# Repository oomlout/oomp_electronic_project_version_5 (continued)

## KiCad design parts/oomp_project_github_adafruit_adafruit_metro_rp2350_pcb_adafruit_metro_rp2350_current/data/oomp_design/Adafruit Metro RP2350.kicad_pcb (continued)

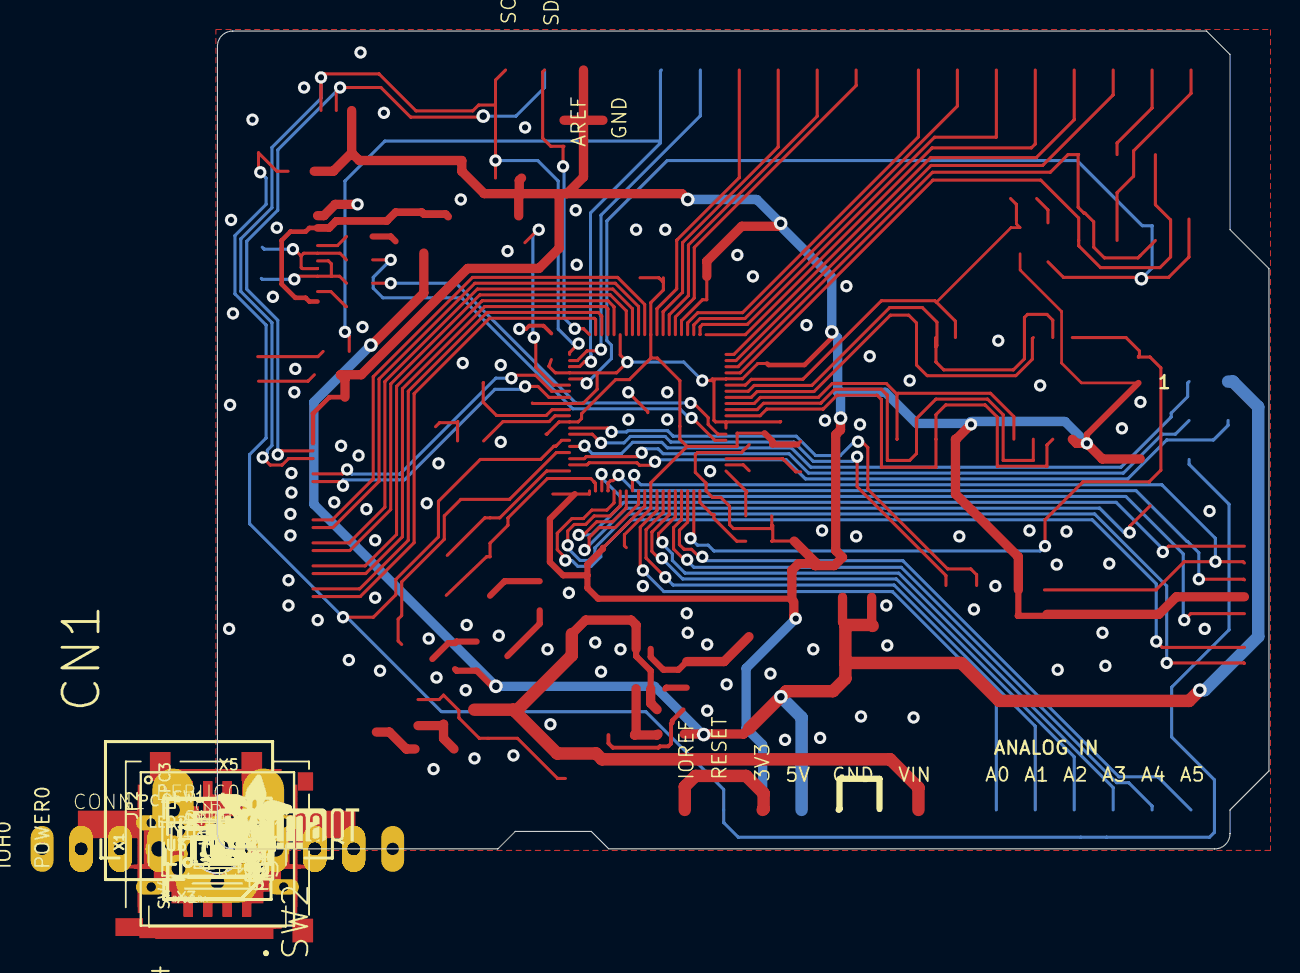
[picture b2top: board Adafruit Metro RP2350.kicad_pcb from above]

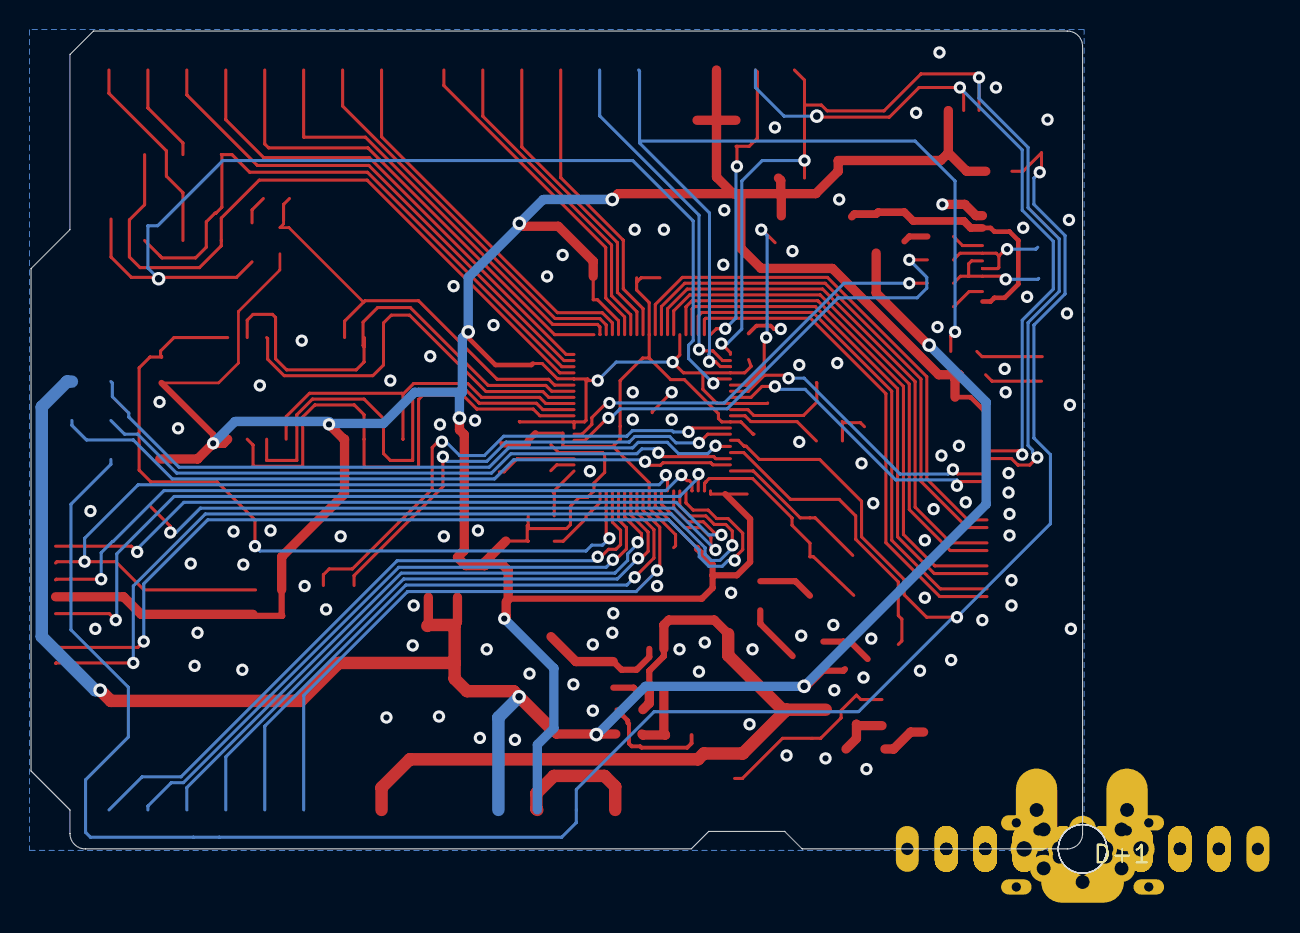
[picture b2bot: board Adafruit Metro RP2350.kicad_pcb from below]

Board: 2 copper layers, 68.6 x 53.3 mm, 174 parts (5 on the bottom side), 89 nets.

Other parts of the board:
PLABEL0: PLABEL0
PLABEL1: PLABEL1
PLABEL2: PLABEL2
PLABEL3: PLABEL3
PLABEL4: PLABEL4
PLABEL5: PLABEL5
PLABEL6: PLABEL6
PLABEL7: PLABEL7
PLABEL8: PLABEL8
PLABEL10: PLABEL10
PLABEL11: PLABEL11
PLABEL12: PLABEL12
PLABEL13: PLABEL13
PLABEL14: PLABEL14
PLABEL15: PLABEL15
PLABEL16: PLABEL16
PLABEL17: PLABEL17
PLABEL18: PLABEL18
PLABEL19: PLABEL19
PLABEL20: PLABEL20
PLABEL21: PLABEL21
PLABEL22: PLABEL22
PLABEL23: PLABEL23
PLABEL24: PLABEL24
PLABEL25: PLABEL25
PLABEL26: PLABEL26
PLABEL27: PLABEL27
PLABEL28: PLABEL28
PLABEL29: PLABEL29
PLABEL30: PLABEL30
PLABEL31: PLABEL31
PLABEL32: PLABEL32
PLABEL33: PLABEL33
PLABEL34: PLABEL34
PLABEL35: PLABEL35
PLABEL36: PLABEL36
PLABEL37: PLABEL37
PLABEL38: PLABEL38
PLABEL39: PLABEL39
PLABEL40: PLABEL40
PLABEL41: PLABEL41
PLABEL42: PLABEL42
PLABEL43: PLABEL43
PLABEL46: PLABEL46
PLABEL47: PLABEL47
PLABEL48: PLABEL48
PLABEL49: PLABEL49
PLABEL50: PLABEL50
PLABEL51: PLABEL51
PLABEL52: PLABEL52
PLABEL53: PLABEL53
PLABEL54: PLABEL54
PLABEL55: PLABEL55
PLABEL56: PLABEL56
PLABEL57: PLABEL57
PLABEL59: PLABEL59
PLABEL60: PLABEL60
PLABEL62: PLABEL62
PLABEL63: PLABEL63
PLABEL64: PLABEL64
PLABEL65: PLABEL65
PLABEL66: PLABEL66
PLABEL67: PLABEL67
PLABEL68: PLABEL68
PLABEL69: PLABEL69
PLABEL70: PLABEL70
U$3: STEMMAQT
U$11: PCBFEAT-REV-040
U$47: METRO_RP2350_TOP
U$50: ADAFRUIT_5MM
U$71: METRO_RP2350_BOT
UNK_HOLE_0: dummyfp0
UNK_HOLE_1: dummyfp1
UNK_HOLE_2: dummyfp2
UNK_HOLE_3: dummyfp3

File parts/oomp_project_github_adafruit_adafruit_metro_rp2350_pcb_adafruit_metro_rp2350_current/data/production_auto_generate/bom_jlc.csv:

Comment,Designator,Footprint,LCSC Part #
,JP1,Adafruit Metro RP2350-import-fps:1X01_ROUND,C7501259
,JP2,Adafruit Metro RP2350-import-fps:1X04_ROUND,C42431795
,U$50,Adafruit Metro RP2350-import-fps:ADAFRUIT_5MM,
,U$71,Adafruit Metro RP2350-import-fps:METRO_RP2350_BOT,
,U$47,Adafruit Metro RP2350-import-fps:METRO_RP2350_TOP,
,U$11,Adafruit Metro RP2350-import-fps:PCBFEAT-REV-040,
,PLABEL0,Adafruit Metro RP2350-import-fps:PLABEL0,
,PLABEL1,Adafruit Metro RP2350-import-fps:PLABEL1,
,PLABEL10,Adafruit Metro RP2350-import-fps:PLABEL10,
,PLABEL11,Adafruit Metro RP2350-import-fps:PLABEL11,
,PLABEL12,Adafruit Metro RP2350-import-fps:PLABEL12,
,PLABEL13,Adafruit Metro RP2350-import-fps:PLABEL13,
,PLABEL14,Adafruit Metro RP2350-import-fps:PLABEL14,
,PLABEL15,Adafruit Metro RP2350-import-fps:PLABEL15,
,PLABEL16,Adafruit Metro RP2350-import-fps:PLABEL16,
,PLABEL17,Adafruit Metro RP2350-import-fps:PLABEL17,
,PLABEL18,Adafruit Metro RP2350-import-fps:PLABEL18,
,PLABEL19,Adafruit Metro RP2350-import-fps:PLABEL19,
,PLABEL2,Adafruit Metro RP2350-import-fps:PLABEL2,
,PLABEL20,Adafruit Metro RP2350-import-fps:PLABEL20,
,PLABEL21,Adafruit Metro RP2350-import-fps:PLABEL21,
,PLABEL22,Adafruit Metro RP2350-import-fps:PLABEL22,
,PLABEL23,Adafruit Metro RP2350-import-fps:PLABEL23,
,PLABEL24,Adafruit Metro RP2350-import-fps:PLABEL24,
,PLABEL25,Adafruit Metro RP2350-import-fps:PLABEL25,
,PLABEL26,Adafruit Metro RP2350-import-fps:PLABEL26,
,PLABEL27,Adafruit Metro RP2350-import-fps:PLABEL27,
,PLABEL28,Adafruit Metro RP2350-import-fps:PLABEL28,
,PLABEL29,Adafruit Metro RP2350-import-fps:PLABEL29,
,PLABEL3,Adafruit Metro RP2350-import-fps:PLABEL3,
,PLABEL30,Adafruit Metro RP2350-import-fps:PLABEL30,
,PLABEL31,Adafruit Metro RP2350-import-fps:PLABEL31,
,PLABEL32,Adafruit Metro RP2350-import-fps:PLABEL32,
,PLABEL33,Adafruit Metro RP2350-import-fps:PLABEL33,
,PLABEL34,Adafruit Metro RP2350-import-fps:PLABEL34,
,PLABEL35,Adafruit Metro RP2350-import-fps:PLABEL35,
,PLABEL36,Adafruit Metro RP2350-import-fps:PLABEL36,
,PLABEL37,Adafruit Metro RP2350-import-fps:PLABEL37,
,PLABEL38,Adafruit Metro RP2350-import-fps:PLABEL38,
,PLABEL39,Adafruit Metro RP2350-import-fps:PLABEL39,
,PLABEL4,Adafruit Metro RP2350-import-fps:PLABEL4,
,PLABEL40,Adafruit Metro RP2350-import-fps:PLABEL40,
,PLABEL41,Adafruit Metro RP2350-import-fps:PLABEL41,
,PLABEL42,Adafruit Metro RP2350-import-fps:PLABEL42,
,PLABEL43,Adafruit Metro RP2350-import-fps:PLABEL43,
,PLABEL46,Adafruit Metro RP2350-import-fps:PLABEL46,
,PLABEL47,Adafruit Metro RP2350-import-fps:PLABEL47,
,PLABEL48,Adafruit Metro RP2350-import-fps:PLABEL48,
,PLABEL49,Adafruit Metro RP2350-import-fps:PLABEL49,
,PLABEL5,Adafruit Metro RP2350-import-fps:PLABEL5,
,PLABEL50,Adafruit Metro RP2350-import-fps:PLABEL50,
,PLABEL51,Adafruit Metro RP2350-import-fps:PLABEL51,
,PLABEL52,Adafruit Metro RP2350-import-fps:PLABEL52,
,PLABEL53,Adafruit Metro RP2350-import-fps:PLABEL53,
,PLABEL54,Adafruit Metro RP2350-import-fps:PLABEL54,
,PLABEL55,Adafruit Metro RP2350-import-fps:PLABEL55,
,PLABEL56,Adafruit Metro RP2350-import-fps:PLABEL56,
,PLABEL57,Adafruit Metro RP2350-import-fps:PLABEL57,
,PLABEL59,Adafruit Metro RP2350-import-fps:PLABEL59,
,PLABEL6,Adafruit Metro RP2350-import-fps:PLABEL6,
,PLABEL60,Adafruit Metro RP2350-import-fps:PLABEL60,
,PLABEL62,Adafruit Metro RP2350-import-fps:PLABEL62,
,PLABEL63,Adafruit Metro RP2350-import-fps:PLABEL63,
,PLABEL64,Adafruit Metro RP2350-import-fps:PLABEL64,
,PLABEL65,Adafruit Metro RP2350-import-fps:PLABEL65,
,PLABEL66,Adafruit Metro RP2350-import-fps:PLABEL66,
,PLABEL67,Adafruit Metro RP2350-import-fps:PLABEL67,
,PLABEL68,Adafruit Metro RP2350-import-fps:PLABEL68,
,PLABEL69,Adafruit Metro RP2350-import-fps:PLABEL69,
,PLABEL7,Adafruit Metro RP2350-import-fps:PLABEL7,
,PLABEL70,Adafruit Metro RP2350-import-fps:PLABEL70,
,PLABEL8,Adafruit Metro RP2350-import-fps:PLABEL8,
,U$3,Adafruit Metro RP2350-import-fps:STEMMAQT,
,TP1,Adafruit Metro RP2350-import-fps:TESTPOINT_ROUND_1.5MM_NO,
0.1uF,"C6,C7,C8,C13,C14,C17,C21,C22,C23,C24,C25,C29,C30,C33",Adafruit Metro RP2350-import-fps:0603-NO,C14663
10,R5,Adafruit Metro RP2350-import-fps:0603-NO,C22859
10K,"R1,R2,R3,R6,R7,R8,R10,R12,R13,R17,R21",Adafruit Metro RP2350-import-fps:0603-NO,C98220
10uF,"C3,C5,C9,C18,C19,C20,C31,C32",Adafruit Metro RP2350-import-fps:0805-NO,
10uF_0603,"C10,C15",Adafruit Metro RP2350-import-fps:0603-NO_WIDE,C19702
12MHz_10pF_50ohm,Y1,Adafruit Metro RP2350-import-fps:CRYSTAL_2.5X2,
15pF,"C26,C27",Adafruit Metro RP2350-import-fps:0603-NO,
1K,"R23,R26",Adafruit Metro RP2350-import-fps:0603-NO,C2907002
1N4148,D3,Adafruit Metro RP2350-import-fps:SOD-323,
1uF,"C2,C11,C12,C16,C28",Adafruit Metro RP2350-import-fps:0603-NO,C5673
2.1mm,X5,Adafruit Metro RP2350-import-fps:DCJACK_2MM_PTH,
2.2K,R11,Adafruit Metro RP2350-import-fps:0603-NO,C4190
2.2uF,"C1,C4",Adafruit Metro RP2350-import-fps:0603-NO,C23630
200,R4,Adafruit Metro RP2350-import-fps:0603-NO,C114664
20609,AD0,Adafruit Metro RP2350-import-fps:1X06_OVALWAVE,C37208
20610,"IOL0,POWER0",Adafruit Metro RP2350-import-fps:1X08_OVALWAVE,C492421
20611,IOH0,Adafruit Metro RP2350-import-fps:1X10_OVALWAVE,C57369
22 ohm,"R24,R25",Adafruit Metro RP2350-import-fps:0603-NO,C23345
220uF/6.3V,PC4,Adafruit Metro RP2350-import-fps:PANASONIC_D,
22p BOTTOM 0.5mm FPC,CN1,Adafruit Metro RP2350-import-fps:FPC_22PIN,
3.3uH 5A 20mOhm,L2,Adafruit Metro RP2350-import-fps:INDUCTOR_0603S,
3x2 M,ICSP0,Adafruit Metro RP2350-import-fps:2X03_ROUND_70MIL,
47uF/25V,PC3,Adafruit Metro RP2350-import-fps:PANASONIC_D,
5.1K,"R19,R20",Adafruit Metro RP2350-import-fps:0603-NO,C23186
56K,R9,Adafruit Metro RP2350-import-fps:0603-NO,C23206
5V/1A,PTC1,Adafruit Metro RP2350-import-fps:0805-NO,
AP2112K-3.3,U2,Adafruit Metro RP2350-import-fps:SOT23-DBV,
BSS138,Q1,Adafruit Metro RP2350-import-fps:SOT23-WIDE,C52895
DFE252012F-3R3M=P2,L1,Adafruit Metro RP2350-import-fps:INDUCTOR_1007,
DMP3098L,"T1,T2",Adafruit Metro RP2350-import-fps:SOT23-WIDE,
DNP,"R14,R15",Adafruit Metro RP2350-import-fps:0603-NO,
DNP,U3,Adafruit Metro RP2350-import-fps:SOIC8_208MIL,
DPDT,SW4,Adafruit Metro RP2350-import-fps:EG1390,
FIDUCIAL_1MM,"FD1,FD2,FD3",Adafruit Metro RP2350-import-fps:FIDUCIAL_1MM,
GREEN,ON0,Adafruit Metro RP2350-import-fps:CHIPLED_0603_NOOUTLINE,
JST_SH3,DEBUG0,Adafruit Metro RP2350-import-fps:JST_SH3_RA,
MICROSD,X1,Adafruit Metro RP2350-import-fps:MOLEX_104031-0811,
PMEG2020,"D1,D2",Adafruit Metro RP2350-import-fps:SOD-323,
RED,L0,Adafruit Metro RP2350-import-fps:CHIPLED_0603_NOOUTLINE,
RP2350B,X4,Adafruit Metro RP2350-import-fps:QFN80,
SPDT_RA,SW1,Adafruit Metro RP2350-import-fps:SPDT_SMT_SSSS811101,
STEMMA_I2C_QT,CONN1,Adafruit Metro RP2350-import-fps:JST_SH4,C160404
SW_RA,"SW2,SW3",Adafruit Metro RP2350-import-fps:SPST_TACTILE_RA,
"TPB1,27","D+1,D-1","Adafruit Metro RP2350-import-fps:B1,27",
TPS563201,IC1,Adafruit Metro RP2350-import-fps:SOT23-6,
USB Type C,X3,Adafruit Metro RP2350-import-fps:USB_C_CUSB31-CFM2AX-01-X,
W25Q128,U6,Adafruit Metro RP2350-import-fps:SOIC8_208MIL,
WS2812B_3535FULL,LED2,Adafruit Metro RP2350-import-fps:LED3535_FULLPADS,

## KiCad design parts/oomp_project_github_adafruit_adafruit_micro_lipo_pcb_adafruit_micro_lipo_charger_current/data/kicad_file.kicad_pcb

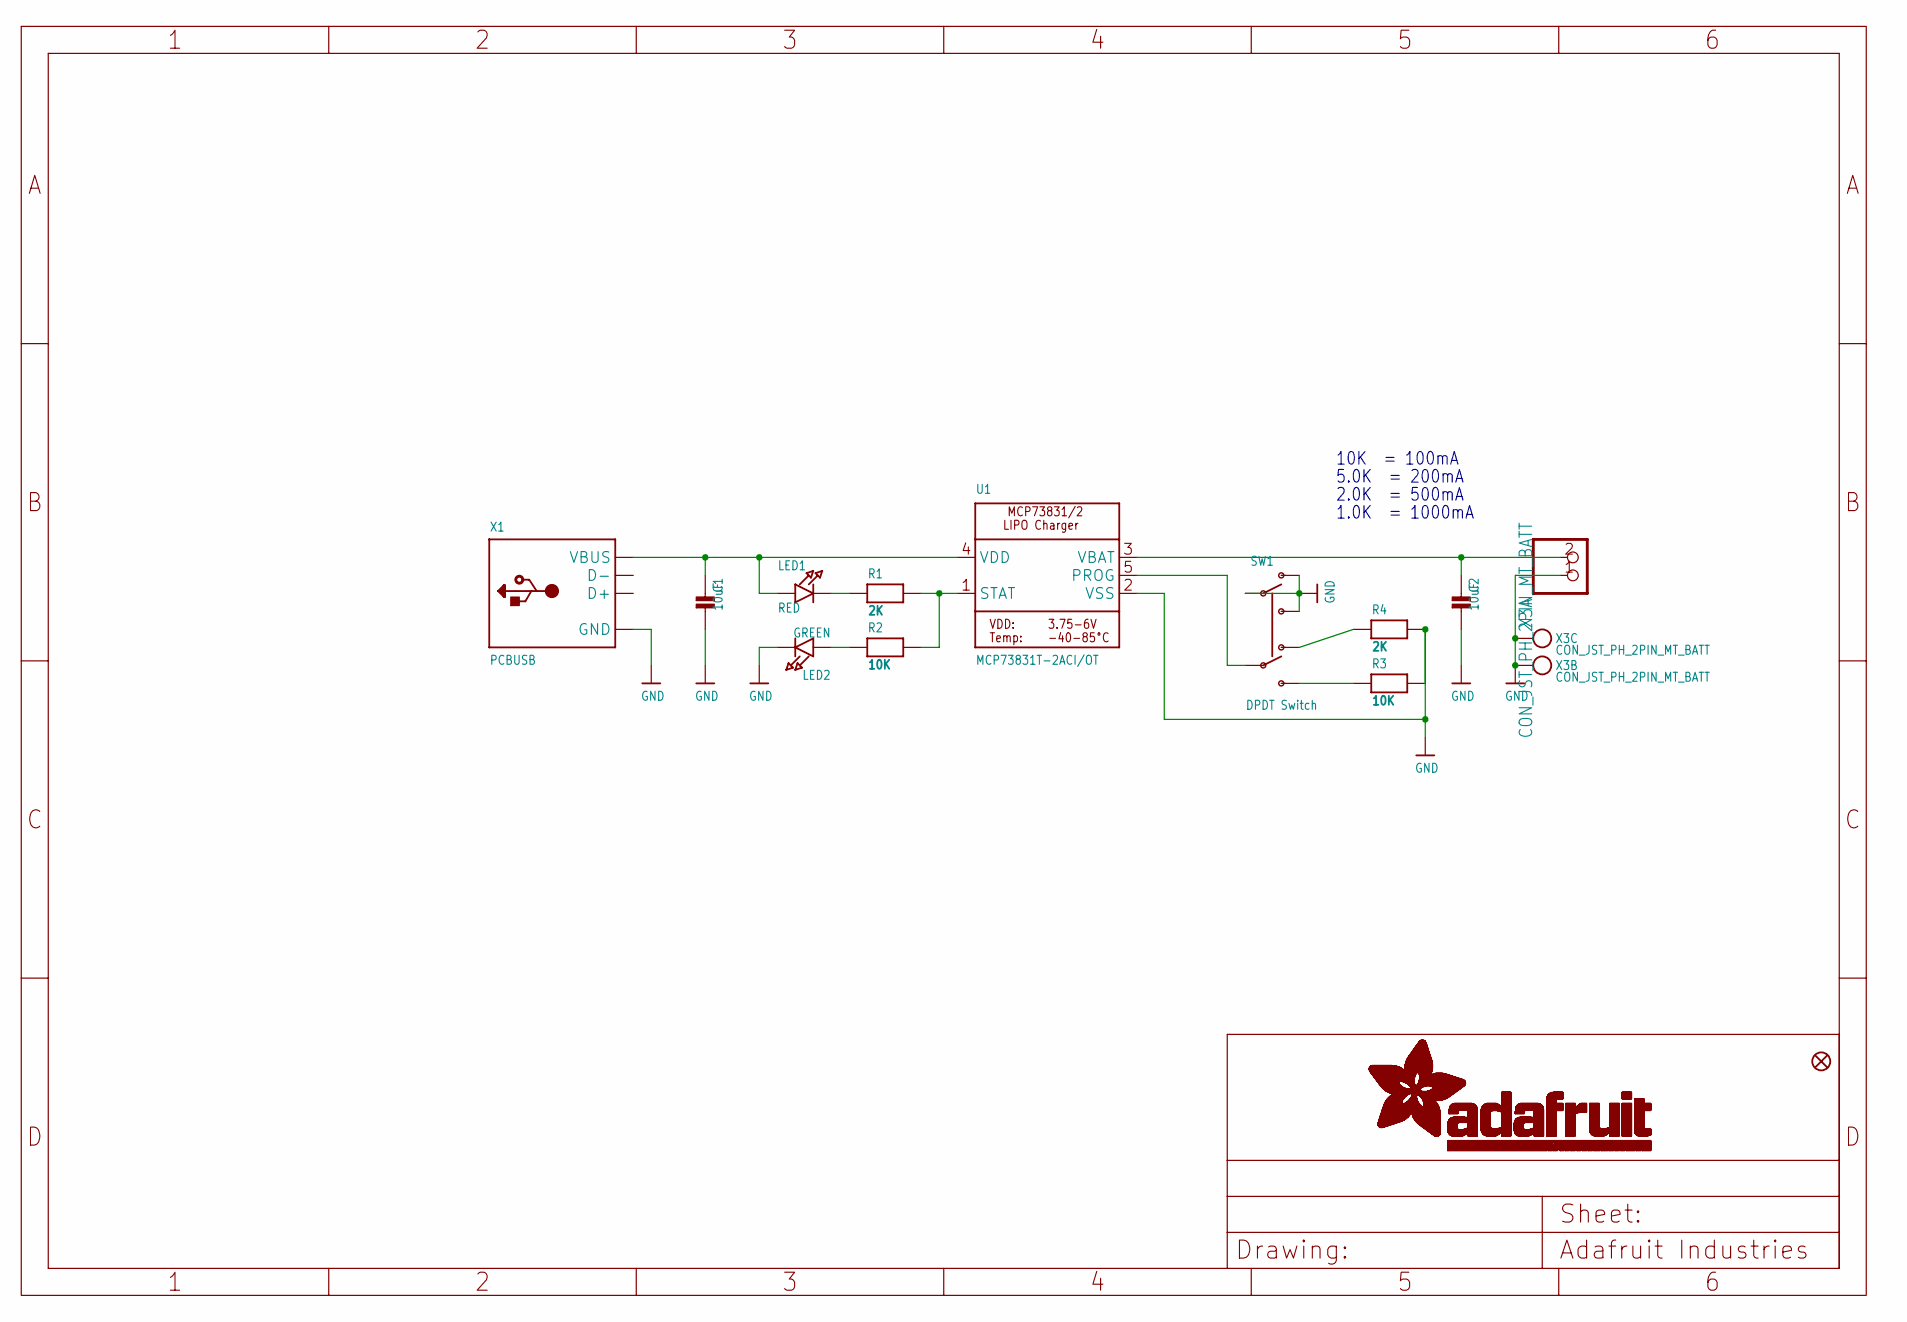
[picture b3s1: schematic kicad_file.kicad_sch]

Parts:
C1, C2: 10uF; 0805-NO
FID1: FIDUCIAL_1MM
LED1: RED; CHIPLED_0603_NOOUTLINE; JLC_ROTATION 270
LED2: GREEN; CHIPLED_0603_NOOUTLINE; JLC_ROTATION 270
R1, R4: 2K; 0603-NO
R2, R3: 10K; 0603-NO
SW1: DPDT Switch; EG1390; LCSC C2837066
U1: MCP73831T-2ACI/OT; SOT23-5; JLC_ROTATION 270
X1: PCBUSB; USBA_PCB
X3: CON_JST_PH_2PIN_MT_BATT; JSTPH2_BATT; LCSC C47647

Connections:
GND: C1.2, C2.2, LED2.C, R3.2, R4.2, SW1.O1, SW1.P1, SW1.S1, U1.2 (VSS), X1.GND, X3.1, X3.NC1, X3.NC2
unnamed: LED1.C, R1.1
unnamed: R1.2, R2.2, U1.1 (STAT)
unnamed: R3.1, SW1.S2
unnamed: R4.1, SW1.O2
unnamed: SW1.P2, U1.5 (PROG)
unnamed: LED2.A, R2.1
VBAT: C2.1, U1.3 (VBAT), X3.2
VDD: C1.1, LED1.A, U1.4 (VDD), X1.VCC (VBUS)

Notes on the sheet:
1.0K = 1000mA
5.0K = 200mA
10K = 100mA
2.0K = 500mA

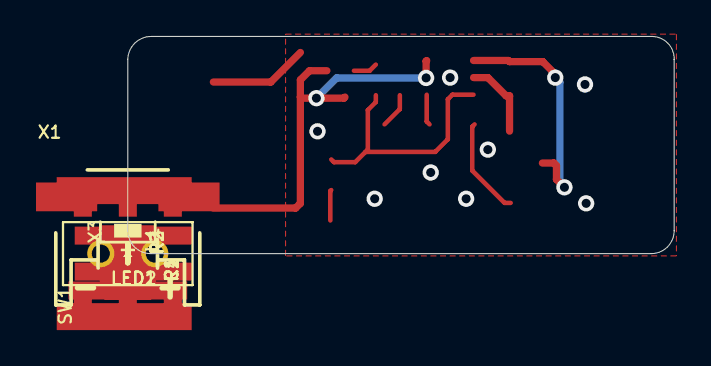
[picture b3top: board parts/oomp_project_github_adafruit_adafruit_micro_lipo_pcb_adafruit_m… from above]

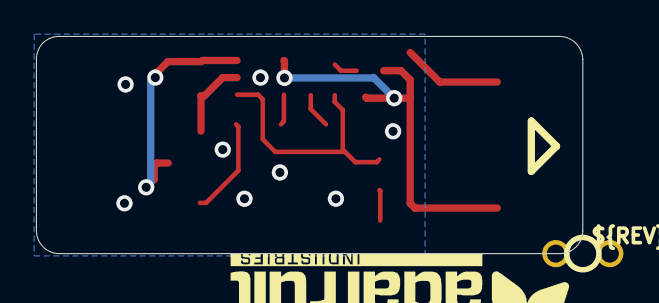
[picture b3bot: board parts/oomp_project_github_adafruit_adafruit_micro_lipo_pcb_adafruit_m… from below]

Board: 2 copper layers, 30.4 x 12.1 mm, 27 parts (5 on the bottom side), 9 nets.

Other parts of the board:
PLABEL0: PLABEL0
PLABEL1: PLABEL1
PLABEL2: PLABEL2
PLABEL3: PLABEL3
PLABEL4: PLABEL4
PLABEL5: PLABEL5
PLABEL6: PLABEL6
PLABEL7: PLABEL7
PLABEL8: PLABEL8
PLABEL9: PLABEL9
PLABEL10: PLABEL10
PLABEL11: PLABEL11
U$8: ADAFRUIT_TEXT_20MM
U$9: PCBFEAT-REV-040

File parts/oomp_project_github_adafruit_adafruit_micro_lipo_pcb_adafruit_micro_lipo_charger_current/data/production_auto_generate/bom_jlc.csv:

Comment,Designator,Footprint,LCSC Part #
,U$8,Adafruit MicroLipo Charger v2-import-fps:ADAFRUIT_TEXT_20MM,
,U$9,Adafruit MicroLipo Charger v2-import-fps:PCBFEAT-REV-040,
,PLABEL0,Adafruit MicroLipo Charger v2-import-fps:PLABEL0,
,PLABEL1,Adafruit MicroLipo Charger v2-import-fps:PLABEL1,
,PLABEL10,Adafruit MicroLipo Charger v2-import-fps:PLABEL10,
,PLABEL11,Adafruit MicroLipo Charger v2-import-fps:PLABEL11,
,PLABEL2,Adafruit MicroLipo Charger v2-import-fps:PLABEL2,
,PLABEL3,Adafruit MicroLipo Charger v2-import-fps:PLABEL3,
,PLABEL4,Adafruit MicroLipo Charger v2-import-fps:PLABEL4,
,PLABEL5,Adafruit MicroLipo Charger v2-import-fps:PLABEL5,
,PLABEL6,Adafruit MicroLipo Charger v2-import-fps:PLABEL6,
,PLABEL7,Adafruit MicroLipo Charger v2-import-fps:PLABEL7,
,PLABEL8,Adafruit MicroLipo Charger v2-import-fps:PLABEL8,
,PLABEL9,Adafruit MicroLipo Charger v2-import-fps:PLABEL9,
10K,"R2,R3",Adafruit MicroLipo Charger v2-import-fps:0603-NO,C98220
10uF,"C1,C2",Adafruit MicroLipo Charger v2-import-fps:0805-NO,
2K,"R1,R4",Adafruit MicroLipo Charger v2-import-fps:0603-NO,C22975
CON_JST_PH_2PIN_MT_BATT,X3,Adafruit MicroLipo Charger v2-import-fps:JSTPH2_BATT,
DPDT Switch,SW1,Adafruit MicroLipo Charger v2-import-fps:EG1390,
GREEN,LED2,Adafruit MicroLipo Charger v2-import-fps:CHIPLED_0603_NOOUTLINE,
MCP73831T-2ACI/OT,U1,Adafruit MicroLipo Charger v2-import-fps:SOT23-5,
PCBUSB,X1,Adafruit MicroLipo Charger v2-import-fps:USBA_PCB,
RED,LED1,Adafruit MicroLipo Charger v2-import-fps:CHIPLED_0603_NOOUTLINE,

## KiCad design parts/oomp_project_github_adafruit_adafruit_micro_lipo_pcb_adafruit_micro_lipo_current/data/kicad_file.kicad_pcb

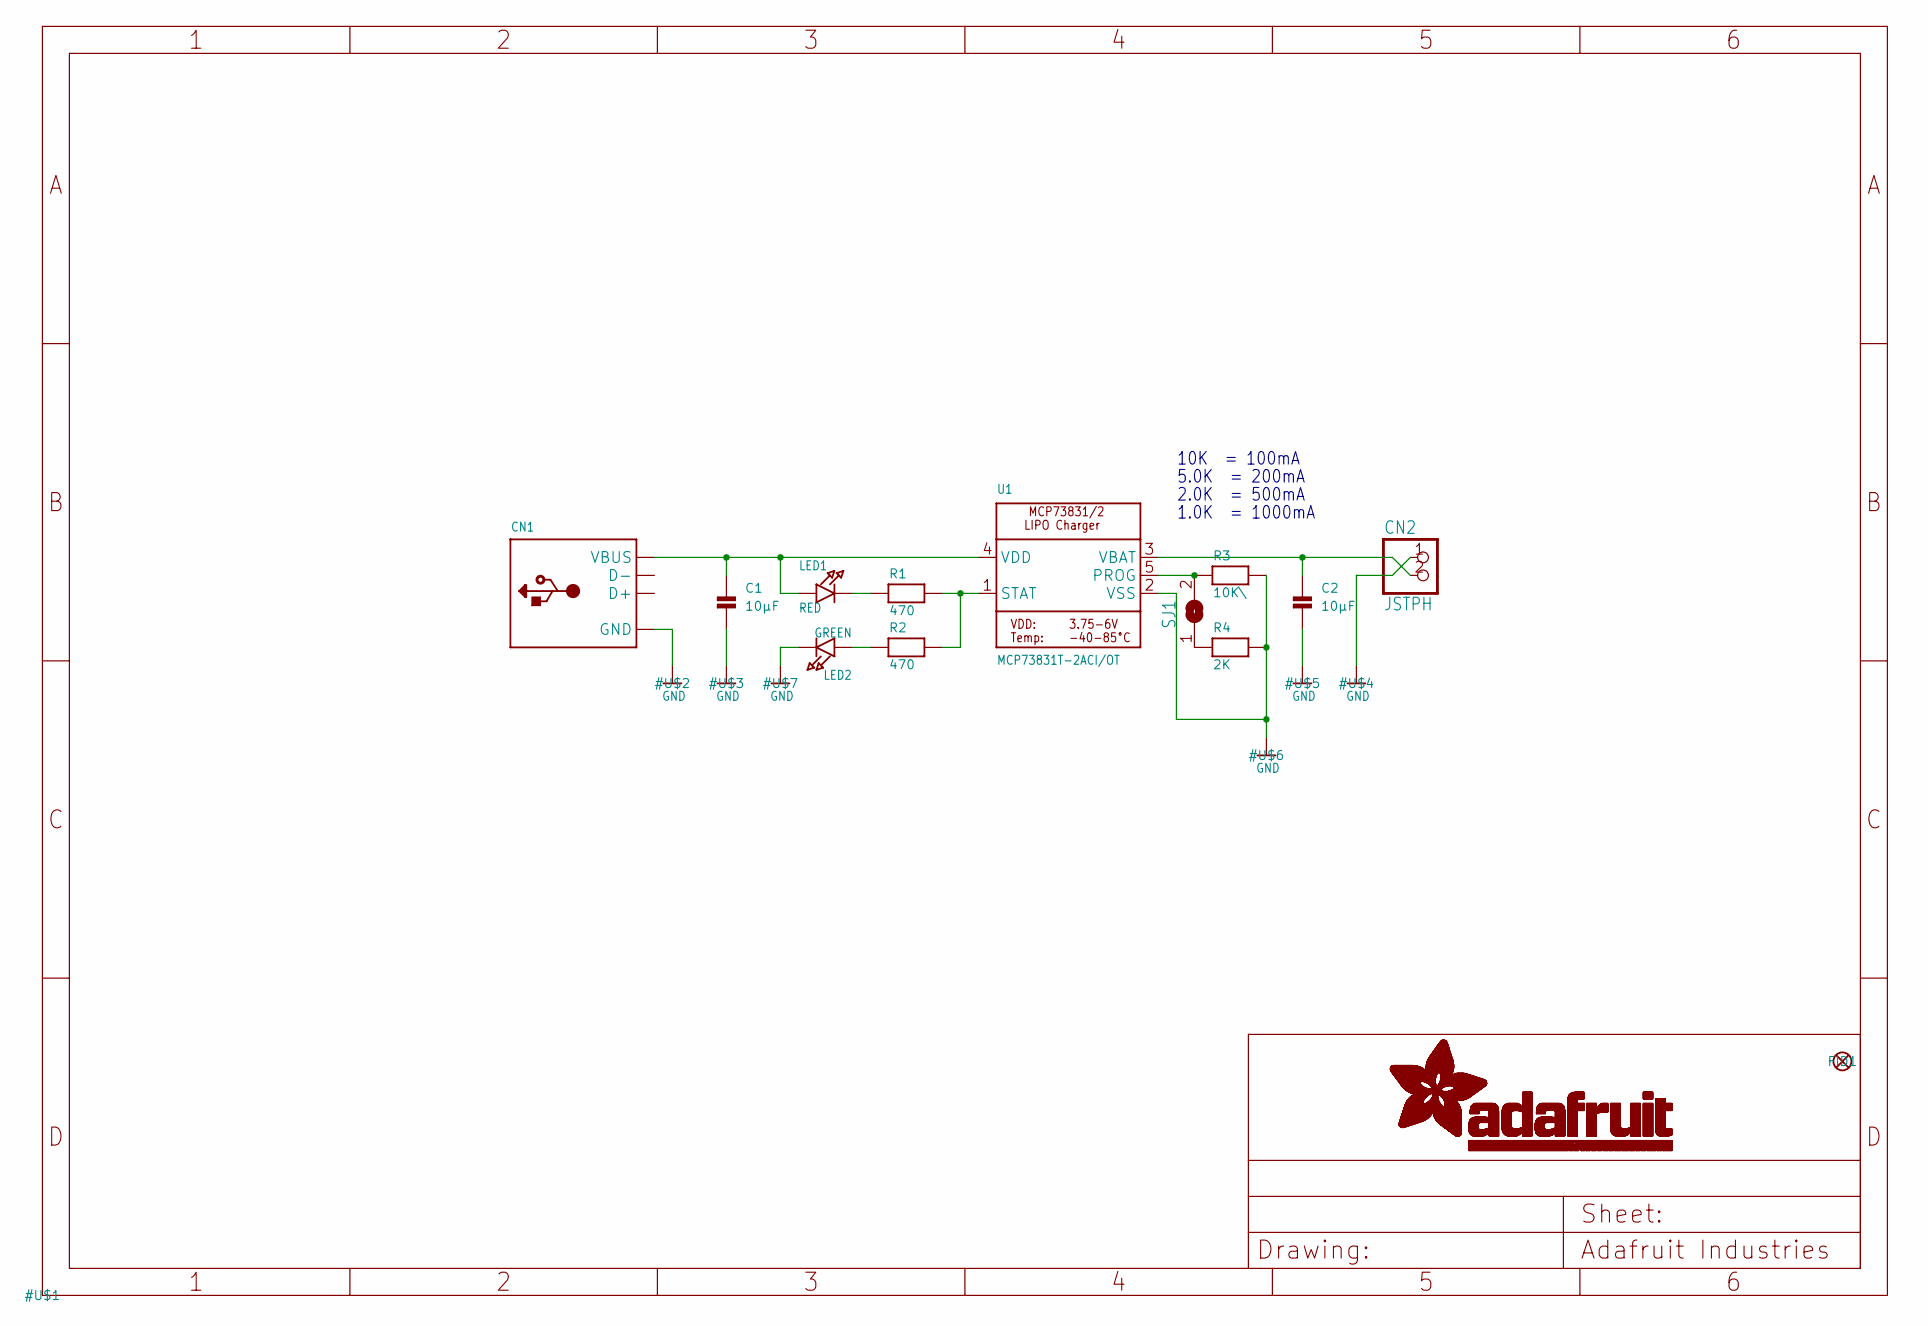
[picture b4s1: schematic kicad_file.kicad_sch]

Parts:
C1, C2: 10µF; 0805
CN1: USB_TYPEAPCB; USBA_PCB
CN2: JSTPH; JSTPH2
FID1: FIDUCIAL""; FIDUCIAL_1MM
LED1: RED; CHIPLED_0805
LED2: GREEN; CHIPLED_0805
R1, R2: 470; 0805
R3: 10K\; 0805
R4: 2K; 0805
SJ1: SOLDERJUMPER; SOLDERJUMPER_ARROW_NOPASTE
U1: MCP73831T-2ACI/OT; SOT23-5

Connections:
GND: C1.2, C2.2, CN1.GND, CN2.1, LED2.C, R3.2, R4.2, U1.2 (VSS)
unnamed: LED1.C, R1.1
unnamed: R1.2, R2.2, U1.1 (STAT)
unnamed: R4.1, SJ1.1
unnamed: R3.1, SJ1.2, U1.5 (PROG)
unnamed: LED2.A, R2.1
VBAT: C2.1, CN2.2, U1.3 (VBAT)
VDD: C1.1, CN1.VCC (VBUS), LED1.A, U1.4 (VDD)

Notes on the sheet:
5.0K = 200mA
10K = 100mA
1.0K = 1000mA
2.0K = 500mA

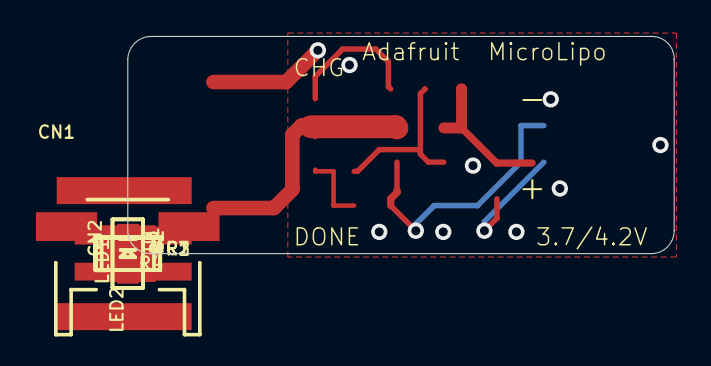
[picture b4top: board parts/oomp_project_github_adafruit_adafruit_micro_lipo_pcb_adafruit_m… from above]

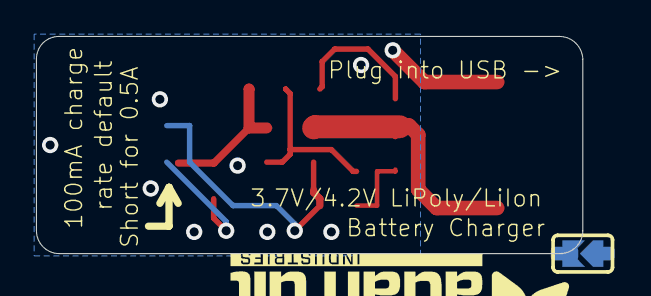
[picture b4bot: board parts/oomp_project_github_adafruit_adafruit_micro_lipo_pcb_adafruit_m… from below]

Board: 2 copper layers, 30.4 x 12.1 mm, 14 parts (2 on the bottom side), 8 nets.

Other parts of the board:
U$8: ADAFRUIT_TEXT_20MM
